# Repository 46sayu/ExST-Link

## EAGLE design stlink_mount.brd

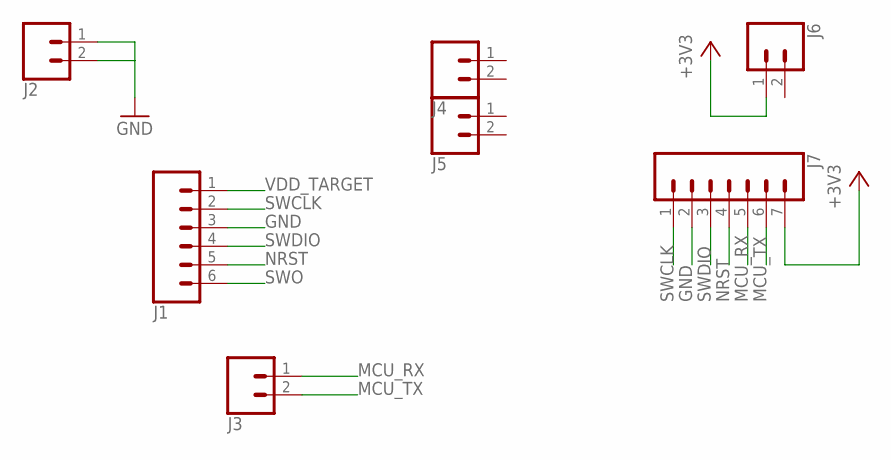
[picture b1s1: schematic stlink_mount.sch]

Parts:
J1: CONN_06SILK_FEMALE_PTH; 1X06
J2, J3, J4, J5, J6: CONN_02; 1X02
J7: CONN_07; 1X07

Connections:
+3V3: J6.1, J7.7
GND: J1.3, J2.1, J2.2, J7.2
MCU_RX: J3.1, J7.5
MCU_TX: J3.2, J7.6
NRST: J1.5, J7.4
SWCLK: J1.2, J7.1
SWDIO: J1.4, J7.3
SWO: J1.6
VDD_TARGET: J1.1

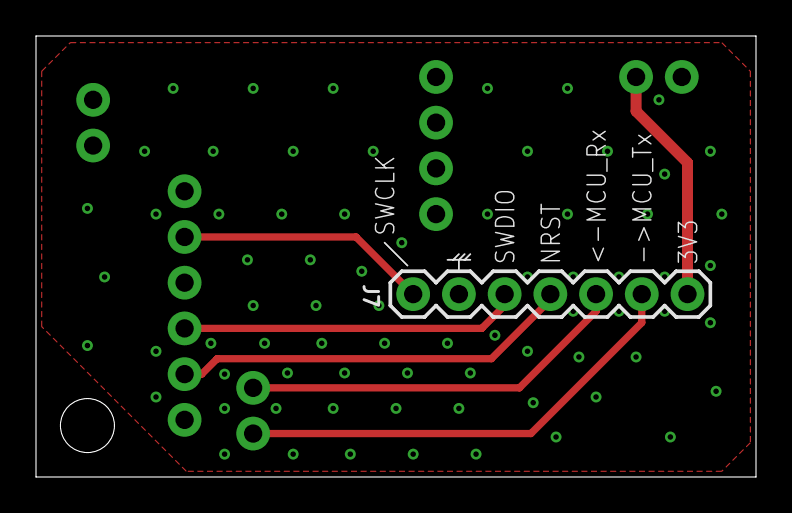
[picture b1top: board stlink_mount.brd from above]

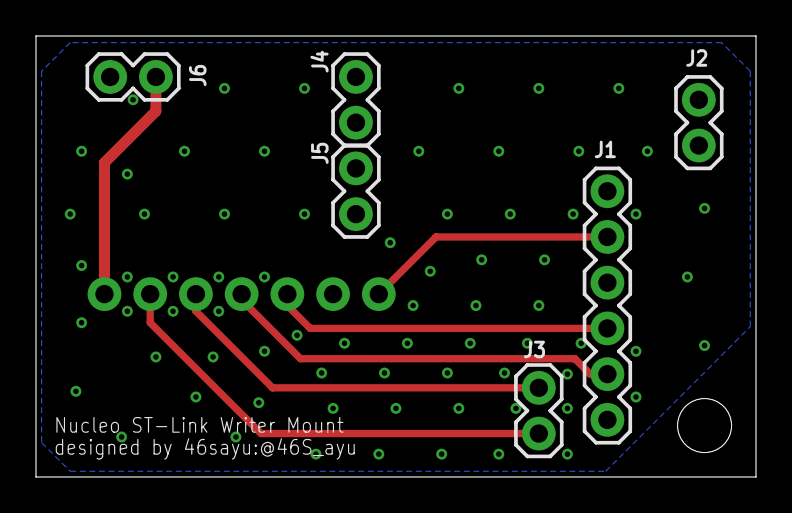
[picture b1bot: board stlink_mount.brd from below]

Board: 2 copper layers, 40.0 x 24.5 mm, 7 parts (6 on the bottom side), 7 nets.

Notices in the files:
parts and their libraries:
SparkFun-Connectors: Licensing: Creative Commons ShareAlike 4.0 International - https://creativecommons.org/licenses/by-sa/4.0
